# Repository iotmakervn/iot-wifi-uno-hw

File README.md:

# iot-wifi-uno-hw

## Features

ESP8266 as Controller compatible with Arduino Uno:  
- Power input 5.5V to 28VDC (1.2A/5V output) and 5V USB
- Automatic enter program mode via Serial - Pre-program OTA firmware
- [ESP8266 Arduino](https://github.com/esp8266/Arduino) and Arduino Library
- Vietnamese doc support from https://esp8266.vn
- Additional Button and LED same NodeMCU.
- Open hardware with CC-BY-SA license
- Design with KiCad

## Hardware

### Schematics

### PCB Layout

### 3D

### Pinout 

### Fritzing part 

### Gerber

[Download](./assets/wifi-uno-hw.zip)

### BOM 

| Designator | Package | Quantity | Designation  |
|-----------------------------------|--------------------------------|----------|--------------|
| U1                                | USB_Micro-B                    | 1        | usb_mini_b   |
| U2                                | MSOP-8_3x3mm_Pitch0.65mm       | 1        | MCP16311-MNY |
| U3                                | SOIC-16_3.9x9.9mm_Pitch1.27mm  | 1        | CH340G       |
| U4                                | ESP-12F                        | 1        | ESP-12E      |
| U5                                | SOT-23-5                       | 1        | MCP6001R     |
| U6                                | HTSOP-J8                       | 1        | BD00GA5WEFJ  |
| U7                                | SOT-23                         | 1        | IRLM6402     |
| D1,D3                             | do214aa                        | 2        | SS24         |
| D2                                | LED_0603                       | 1        | LED_Blue     |
| D4                                | LED_0603                       | 1        | L_PWR_VANG   |
| D5                                | SOD-80                         | 1        | ZENER_3.3V   |
| X1                                | Crystal_SMD_3225_4Pads         | 1        | 12MHz        |
| Q1,Q2                             | SOT-23                         | 2        | MMBT8050LT1G |
| L1                                | Choke_SMD_Wuerth-WE-PD2-Typ-MS | 1        | 22uH         |
| CON1                              | BARREL_JACK                    | 1        | BARREL_JACK  |
| C3,C4.C10,C11                     | C_1210                         | 4        | 10uF/50V     |
| C13                               | C_1210                         | 1        | 1uF/25V      |
| C1,C2                             | C_0603                         | 2        | 22pF         |
| C15,C7                            | C_0603                         | 2        | 1uF/25V      |
| C6,C8,C9,C12,C14,C5               | C_0603                         | 6        | 100nF        |
| R1,R2,R3,R4,R5,R9,R18,R19,R10,R11 | R_0603                         | 10       | 10k          |
| R6,R7,R12,R14,R17,R22             | R_0603                         | 6        | 470R         |
| R8                                | R_0603                         | 1        | 52.5K        |
| R13                               | R_0603                         | 1        | 0R           |
| R15                               | R_0603                         | 1        | 220k/1%      |
| R16                               | R_0603                         | 1        | 100k/1%      |
| R20                               | R_0603                         | 1        | 3K/1%        |
| R21                               | R_0603                         | 1        | 1K/1%        |
| P5                                | Pin_Header_Straight_1x04       | 1        | CONN_01X04   |
| P2,P1                             | Pin_Header_Straight_1x08       | 2        | CONN_01X08   |
| P3                                | Pin_Header_Straight_1x06       | 1        | CONN_01X06   |
| P4                                | Pin_Header_Straight_1x10       | 1        | CONN_01X10   |

### Remark

This project was in development phase - we will remove this remark after release

# License

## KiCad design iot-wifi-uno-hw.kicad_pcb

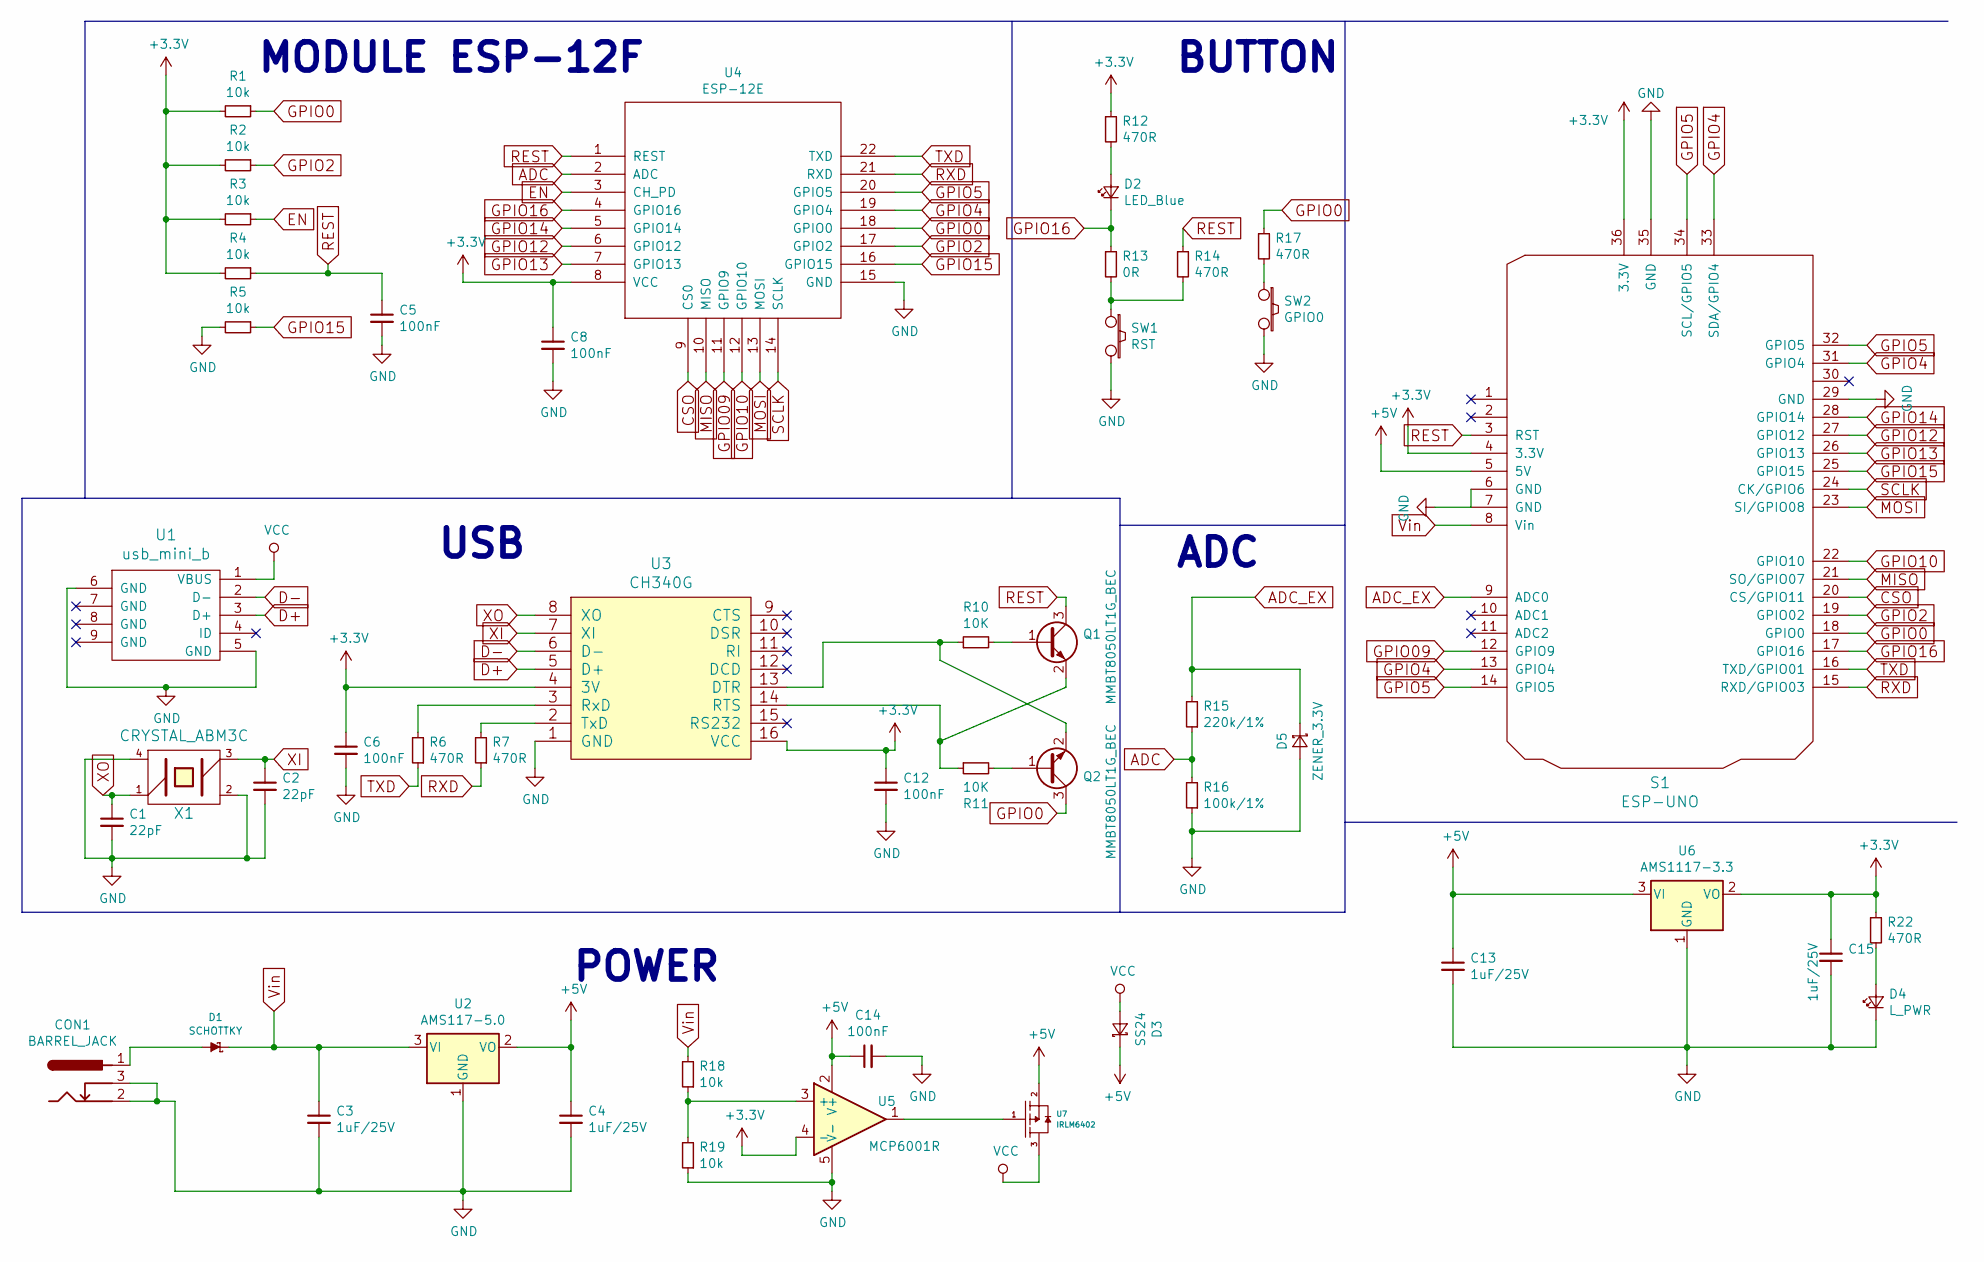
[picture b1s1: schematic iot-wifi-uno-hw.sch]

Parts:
C1, C2: 22pF; C_0603
C3, C4, C13: 1uF/25V; C_1210
C5, C6, C8, C12, C14: 100nF; C_0603
C15: 1uF/25V; C_0603
CON1: BARREL_JACK
D1: SCHOTTKY; do214aa-g
D2: LED_Blue; LED_0603
D3: SS24; do214aa-g
D4: L_PWR; LED_0603
D5: ZENER_3.3V; SOD-80
Q1, Q2: MMBT8050LT1G_BEC; SOT-23
R1, R2, R3, R4, R5, R18, R19: 10k; R_0603
R6, R7, R12, R14, R17, R22: 470R; R_0603
R10, R11: 10K; R_0603
R13: 0R; R_0603
R15: 220k/1%; R_0603
R16: 100k/1%; R_0603
S1: ESP-UNO; shield-uno
SW1: RST; Tact_Switch_TS6X3.6
SW2: GPIO0; Tact_Switch_TS6X3.6
U1: usb_mini_b; USB_Micro-B
U2: AMS117-5.0; SOT-223-3Lead_TabPin2
U3: CH340G; SOIC-16_3.9x9.9mm_Pitch1.27mm
U4: ESP-12E; ESP-12F
U5: MCP6001R; SOT-23-5
U6: AMS1117-3.3; SOT-223-3Lead_TabPin2
U7: IRLM6402; SOT-23
X1: CRYSTAL_ABM3C; Crystal_SMD_3225_4Pads

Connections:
+3V3: C6.1, C8.1, C12.1, C15.1, R1.2, R2.2, R3.2, R4.2, R12.1, R22.1, S1.4 (3.3V), S1.36 (3.3V), U3.4 (3V), U3.16 (VCC), U4.8 (VCC), U5.4 (-), U6.2 (VO)
+5V: C4.1, C13.1, C14.1, D3.1 (K), S1.5 (5V), U2.2 (VO), U5.2 (V+), U6.3 (VI), U7.2
ADC: R15.1, R16.2, U4.2 (ADC)
ADC_EX: D5.1 (K), R15.2, S1.9 (ADC0)
CSO: S1.20 (CS/GPIO11), U4.9 (CS0)
D+: U1.3 (D+), U3.5 (D+)
D-: U1.2 (D-), U3.6 (D-)
EN: R3.1, U4.3 (CH_PD)
GND: C1.2, C2.2, C3.2, C4.2, C5.2, C6.2, C8.2, C12.2, C13.2, C14.2, C15.2, CON1.2, CON1.3, D4.1 (K), D5.2 (A), R5.2, R16.1, R19.1, S1.6 (GND), S1.7 (GND), S1.29 (GND), S1.35 (GND), SW1.2, SW2.2, U1.5 (GND), U1.6 (GND), U2.1 (GND), U3.1 (GND), U4.15 (GND), U5.5 (V-), U6.1 (GND), X1.2 (GND), X1.4 (GND)
GPIO0: Q2.3 (C), R1.1, R17.1, S1.18 (GPIO0~), U4.18 (GPIO0)
GPIO2: R2.1, S1.19 (GPIO02), U4.17 (GPIO2)
GPIO4: S1.13 (GPIO4), S1.31 (GPIO4), S1.33 (SDA/GPIO4), U4.19 (GPIO4)
GPIO5: S1.14 (GPIO5), S1.32 (GPIO5), S1.34 (SCL/GPIO5), U4.20 (GPIO5)
GPIO09: S1.12 (GPIO9), U4.11 (GPIO9)
GPIO10: S1.22 (GPIO10), U4.12 (GPIO10)
GPIO12: S1.27 (GPIO12), U4.6 (GPIO12)
GPIO13: S1.26 (GPIO13), U4.7 (GPIO13)
GPIO14: S1.28 (GPIO14), U4.5 (GPIO14)
GPIO15: R5.1, S1.25 (GPIO15), U4.16 (GPIO15)
GPIO16: D2.1 (K), R13.1, S1.17 (GPIO16~), U4.4 (GPIO16)
MISO: S1.21 (SO/GPIO07~), U4.10 (MISO)
MOSI: S1.23 (SI/GPIO08), U4.13 (MOSI)
unnamed: CON1.1, D1.1 (A)
unnamed: D2.2 (A), R12.2
unnamed: D4.2 (A), R22.2
unnamed: Q1.1 (B), R10.2
unnamed: Q1.2 (E), R11.1, U3.14 (RTS)
unnamed: Q2.1 (B), R11.2
unnamed: Q2.2 (E), R10.1, U3.13 (DTR)
unnamed: R6.2, U3.3 (RxD)
unnamed: R7.2, U3.2 (TxD)
unnamed: R13.2, R14.2, SW1.1
unnamed: R17.2, SW2.1
unnamed: R18.1, R19.2, U5.3 (+)
unnamed: U5.1, U7.1
REST: C5.1, Q1.3 (C), R4.1, R14.1, S1.3 (RST), U4.1 (REST)
RXD: R7.1, S1.15 (RXD/GPIO03), U4.21 (RXD)
SCLK: S1.24 (CK/GPIO6~), U4.14 (SCLK)
TXD: R6.1, S1.16 (TXD/GPIO01), U4.22 (TXD)
VCC: D3.2 (A), U1.1 (VBUS), U7.3
Vin: C3.1, D1.2 (K), R18.2, S1.8 (Vin), U2.3 (VI)
XI: C2.1, U3.7 (XI), X1.3
XO: C1.1, U3.8 (XO), X1.1

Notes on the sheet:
ADC
USB
POWER
MODULE ESP-12F
BUTTON

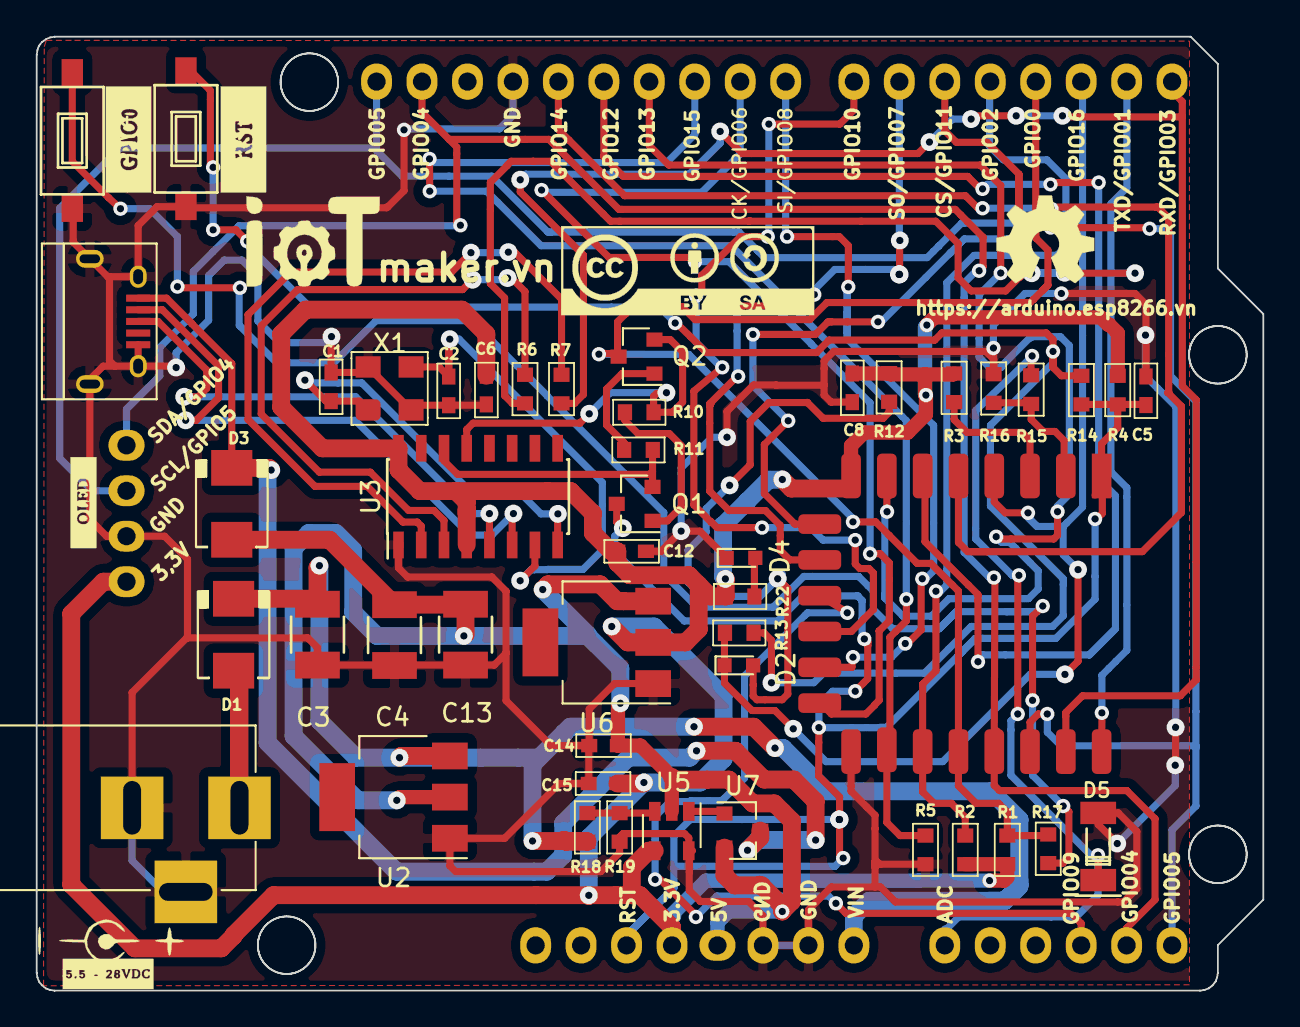
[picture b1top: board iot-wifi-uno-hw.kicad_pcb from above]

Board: 2 copper layers, 68.5 x 53.3 mm, 48 parts (0 on the bottom side), 43 nets.

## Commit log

2016-11-13 change to New Source
2016-11-14 final schematic
2016-11-14 add PCB
2016-11-15 add VIN
2016-11-15 add VIN to PCB - MOSFET & OpAmp
2016-11-15 Completed PCB
2016-11-15 modify track & silk
    - rotate label same heading with component
    - move some track
2016-11-15 Fix Picture 3D in README
2016-11-15 add picture 3D
2016-11-16 modify lodo IoT & link esp8266.vn and add gerber file
2016-11-16 update gerber file
2016-11-16 modify logo & update picture
2016-11-16 update English readme and license
2016-11-16 update remark
2016-11-22 New PCB (#9)
    * fix via beetwen U3 & R16
    * Delete fp-lib-table
    * deleted iot-wifi-uno-hw-cache.lib
    * Fix crystall of CH340G
    * modify some track
    * Modify footprint MCP16311, add zener to ADC, fix footprint 2 transistor
2016-11-22 correct zener placement
2016-11-23 Completed PCB (#10)
    * fix via beetwen U3 & R16
    * Delete fp-lib-table
    * deleted iot-wifi-uno-hw-cache.lib
    * Fix crystall of CH340G
    * modify some track
    * Modify footprint MCP16311, add zener to ADC, fix footprint 2 transistor
2016-11-23 Fix Zone at module ESP-12 (#11)
    * fix via beetwen U3 & R16
    * Delete fp-lib-table
    * deleted iot-wifi-uno-hw-cache.lib
    * Fix crystall of CH340G
    * modify some track
    * Modify footprint MCP16311, add zener to ADC, fix footprint 2 transistor
2016-11-23 remove supply ref column on BOM list
2016-11-24 add fritzing part
2016-11-24 Fix pinout transistor (#12)
    * fix via beetwen U3 & R16
    * Delete fp-lib-table
    * deleted iot-wifi-uno-hw-cache.lib
    * Fix crystall of CH340G
    * modify some track
    * Modify footprint MCP16311, add zener to ADC, fix footprint 2 transistor
2016-11-26 Fix Via for easy make PCB (#13)
    * fix via beetwen U3 & R16
    * Delete fp-lib-table
    * deleted iot-wifi-uno-hw-cache.lib
    * Fix crystall of CH340G
    * modify some track
    * Modify footprint MCP16311, add zener to ADC, fix footprint 2 transistor
2016-12-13 Add Pinout file (#14)
    * fix via beetwen U3 & R16
    * Delete fp-lib-table
    * deleted iot-wifi-uno-hw-cache.lib
    * Fix crystall of CH340G
    * modify some track
    * Modify footprint MCP16311, add zener to ADC, fix footprint 2 transistor
2017-04-03 Fix error button & modify pwr for CH340G 5v to 3.3V (#15)
    * fix via beetwen U3 & R16
    * Delete fp-lib-table
    * deleted iot-wifi-uno-hw-cache.lib
    * Fix crystall of CH340G
    * modify some track
    * Modify footprint MCP16311, add zener to ADC, fix footprint 2 transistor
2017-11-02 feature/power (#16)
    * ?
    * edited pcb
    * pcb layout hoan chỉnh
    * pcb layout hoàn chỉnh
    * pcb layout hoàn chỉnh
    * Update .gitignore

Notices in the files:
README.md:
License:
http://mirrors.creativecommons.org/presskit/buttons/88x31/png/by-sa.png
